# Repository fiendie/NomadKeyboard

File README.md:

# Nomad Keyboard

The Nomad is a 7×5 keys, column-staggered split keyboard based in part on the [Sofle Choc by Brian Low](https://github.com/brianlow/SofleKeyboard).
It uses low profile Kailh Choc v1 switches with hotswap sockets and features per-key RGB lighting via SK6812 Mini-E LEDs.
Compared to the Sofle Choc the nomad offers an additional thumb cluster key, an additional modifier key in the 5th row and a 7th inner column with 3 keys each.
An MX version is also available.

If you are a non-EU resident you can buy pre-made keyboards from [Lucky Boy Store](https://www.aliexpress.com/item/1005009922158971.html) on AliExpress.

## Table of Contents

- [Firmware](#firmware)
- [Bill of Materials](#bill-of-materials)
- [Default Layout](#default-layout)
- [Build Instructions](#build-instructions)
- [Images](#images)

## Firmware 

Nomad uses [QMK firmware](https://github.com/fiendie/qmk_firmware/tree/nomad)

Currently there is a default keymap for and a vial keymap to configure your keyboard in real time.

## Bill of Materials

| **Item**                                 | **Quantity** | **Notes**                                                                       |
|------------------------------------------|--------------|---------------------------------------------------------------------------------|
| **Nomad PCB**                            | 2            | Custom left and right halves.                                                   |
| **Kailh Choc v1 or MX switches**         | 68           | Choose based on version, the Choc version is only compatible with v1 switches!. |
| **Keycaps (MBK, ChocFox, or MX)**        | 68           | Must match switch type and profile preference.                                  |
| **SMD Diodes (1N4148, 0805 package)**    | 68           | One per switch; surface-mount only.                                             |
| **SK6812 Mini-E LEDs**                   | 68           | One per switch, make sure you get the Mini-E version specifically.              |
| **RP2040 Controller**                    | 2            | Tested with SplitKB Liatris and 42.Keebs Frood.                                 |
| **TRRS jacks**                           | 2            | For inter-half communication.                                                   |
| **TRRS cable**                           | 1            | Male-to-male, preferrably with 90 degree plugs                                  |
| **ALPS EC12 Low-Profile Rotary Encoder** | 2            | Optional rotary input.                                                          |
| **Tactile Reset Button**                 | 2            | Optional but useful.                                                            |
| **OLED Display (SSD1306 128x32)**        | 2 (optional) | Optional I2C displays.                                                          |
| **SMD Resistors (0805 package)**         | 4            | I2C pull-up resistors, ony needed for the displays                              |
| **Header Pins**                          | Varies       | For MCU, OLEDs.                                                                 |
| **3D-Printed Case**                      | 2 halves     | Top shell only; open-bottom design using included STL files.                    |
| **Acrylic Cover**                        | 2 halves     | Laser-cut cover layer using included DXF file.                                  |
| **M2 Standoffs (12 mm)**                 | 8            | For mounting cover to case.                                                     |
| **M2 Countersunk Screws (top)**          | 8            | For securing the acrylic cover to standoffs.                                    |
| **M2 Hex Screws (bottom of standoffs)**  | 8            | Attach standoffs from underneath the case edge.                                 |
| **Rubber feet**                          | 8+           | Optional, for grip and elevation.                                               |

## Default layout 

**Base Layer**
```
┌──────┬─────┬─────┬─────┬─────┬─────┬─────┐                ┌─────┬─────┬─────┬─────┬─────┬─────┬──────┐
│ Esc  │  1  │  2  │  3  │  4  │  5  │  <  │                │  >  │  6  │  7  │  8  │  9  │  0  │ Bksp │
├──────┼─────┼─────┼─────┼─────┼─────┼─────┤                ├─────┼─────┼─────┼─────┼─────┼─────┼──────┤
│ Tab  │  Q  │  W  │  E  │  R  │  T  │  {  │                │  }  │  Z  │  U  │  I  │  O  │  P  │  ?   │
├──────┼─────┼─────┼─────┼─────┼─────┼─────┤                ├─────┼─────┼─────┼─────┼─────┼─────┼──────┤
│  =   │  A  │  S  │  D  │  F  │  G  │  |  │                │  -  │  H  │  J  │  K  │  L  │  +  │  #   │
├──────┼─────┼─────┼─────┼─────┼─────┼─────┘                └─────┼─────┼─────┼─────┼─────┼─────┼──────┤
│ LSft │  Y  │  X  │  C  │  V  │  B  │                            │  N  │  M  │  ,  │  .  │  ↑  │ RSft │
├──────┼─────┼─────┼─────┼─────┼─────┼─────┬─────┐    ┌─────┬─────┼─────┼─────┼─────┼─────┼─────┼──────┤
│ Ctrl │ L3  │ L2  │ Opt │ GUI │     │ Spc │ Del │    │ L1  │ Rtn │     │ GUI │ Opt │  ←  │  ↓  │  →   │
└──────┴─────┴─────┴─────┴─────┘     └─────┴─────┘    └─────┴─────┘     └─────┴─────┴─────┴─────┴──────┘
```
**Symbol Layer**
```
┌──────┬─────┬─────┬─────┬─────┬─────┬─────┐                ┌─────┬─────┬─────┬─────┬─────┬─────┬──────┐
│      │     │     │     │     │     │  ^  │                │  °  │     │     │     │     │     │      │
├──────┼─────┼─────┼─────┼─────┼─────┼─────┤                ├─────┼─────┼─────┼─────┼─────┼─────┼──────┤
│      │  Q  │     │  €  │     │     │  [  │                │  ]  │     │  Ü  │     │  Ö  │     │      │
├──────┼─────┼─────┼─────┼─────┼─────┼─────┤                ├─────┼─────┼─────┼─────┼─────┼─────┼──────┤
│      │  Ä  │  ß  │     │     │     │  \  │                │  /  │  H  │     │     │  @  │     │      │
├──────┼─────┼─────┼─────┼─────┼─────┼─────┘                └─────┼─────┼─────┼─────┼─────┼─────┼──────┤
│      │     │     │     │     │     │                            │  ~  │     │     │     │     │      │
├──────┼─────┼─────┼─────┼─────┼─────┼─────┬─────┐    ┌─────┬─────┼─────┼─────┼─────┼─────┼─────┼──────┤
│      │     │     │     │     │     │     │     │    │     │     │     │     │     │     │     │      │
└──────┴─────┴─────┴─────┴─────┘     └─────┴─────┘    └─────┴─────┘     └─────┴─────┴─────┴─────┴──────┘
```
**FN/Media Layer**
```
┌──────┬─────┬─────┬─────┬─────┬─────┬─────┐                ┌─────┬─────┬─────┬─────┬─────┬─────┬──────┐
│      │ F1  │ F2  │ F3  │ F4  │ F5  │ F6  │                │ F7  │ F8  │ F9  │ F10 │ F11 │ F12 │      │
├──────┼─────┼─────┼─────┼─────┼─────┼─────┤                ├─────┼─────┼─────┼─────┼─────┼─────┼──────┤
│      │     │     │     │     │     │     │                │ B+  │     │     │     │     │     │      │
├──────┼─────┼─────┼─────┼─────┼─────┼─────┤                ├─────┼─────┼─────┼─────┼─────┼─────┼──────┤
│      │     │     │     │     │     │     │                │ B-  │     │     │     │     │     │      │
├──────┼─────┼─────┼─────┼─────┼─────┼─────┘                └─────┼─────┼─────┼─────┼─────┼─────┼──────┤
│      │     │     │     │     │     │                            │     │     │     │     │ PgU │ Ins  │
├──────┼─────┼─────┼─────┼─────┼─────┼─────┬─────┐    ┌─────┬─────┼─────┼─────┼─────┼─────┼─────┼──────┤
│      │     │     │     │ Rwd │     │ Pla │ Mut │    │ V-  │ V+  │     │ Fwd │     │ Hom │ PgD │ End  │
└──────┴─────┴─────┴─────┴─────┘     └─────┴─────┘    └─────┴─────┘     └─────┴─────┴─────┴─────┴──────┘
```
**RGB Settings Layer**
```
┌──────┬─────┬─────┬─────┬─────┬─────┬─────┐                ┌─────┬─────┬─────┬─────┬─────┬─────┬──────┐
│      │     │     │     │     │     │ Tgl │                │     │     │     │     │     │     │      │
├──────┼─────┼─────┼─────┼─────┼─────┼─────┤                ├─────┼─────┼─────┼─────┼─────┼─────┼──────┤
│      │     │     │     │     │     │ Md- │                │ Md+ │     │     │     │     │     │      │
├──────┼─────┼─────┼─────┼─────┼─────┼─────┤                ├─────┼─────┼─────┼─────┼─────┼─────┼──────┤
│      │     │     │     │     │     │ Sp- │                │ Sp+ │     │     │     │     │     │      │
├──────┼─────┼─────┼─────┼─────┼─────┼─────┘                └─────┼─────┼─────┼─────┼─────┼─────┼──────┤
│      │     │     │     │     │     │                            │     │     │     │     │     │      │
├──────┼─────┼─────┼─────┼─────┼─────┼─────┬─────┐    ┌─────┬─────┼─────┼─────┼─────┼─────┼─────┼──────┤
│      │     │     │     │ Va- │     │ H-  │ H+  │    │ S-  │ S+  │     │ Va+ │     │     │     │      │
└──────┴─────┴─────┴─────┴─────┘     └─────┴─────┘    └─────┴─────┘     └─────┴─────┴─────┴─────┴──────┘
```

## Build Instructions

Still a work in progress

## Images

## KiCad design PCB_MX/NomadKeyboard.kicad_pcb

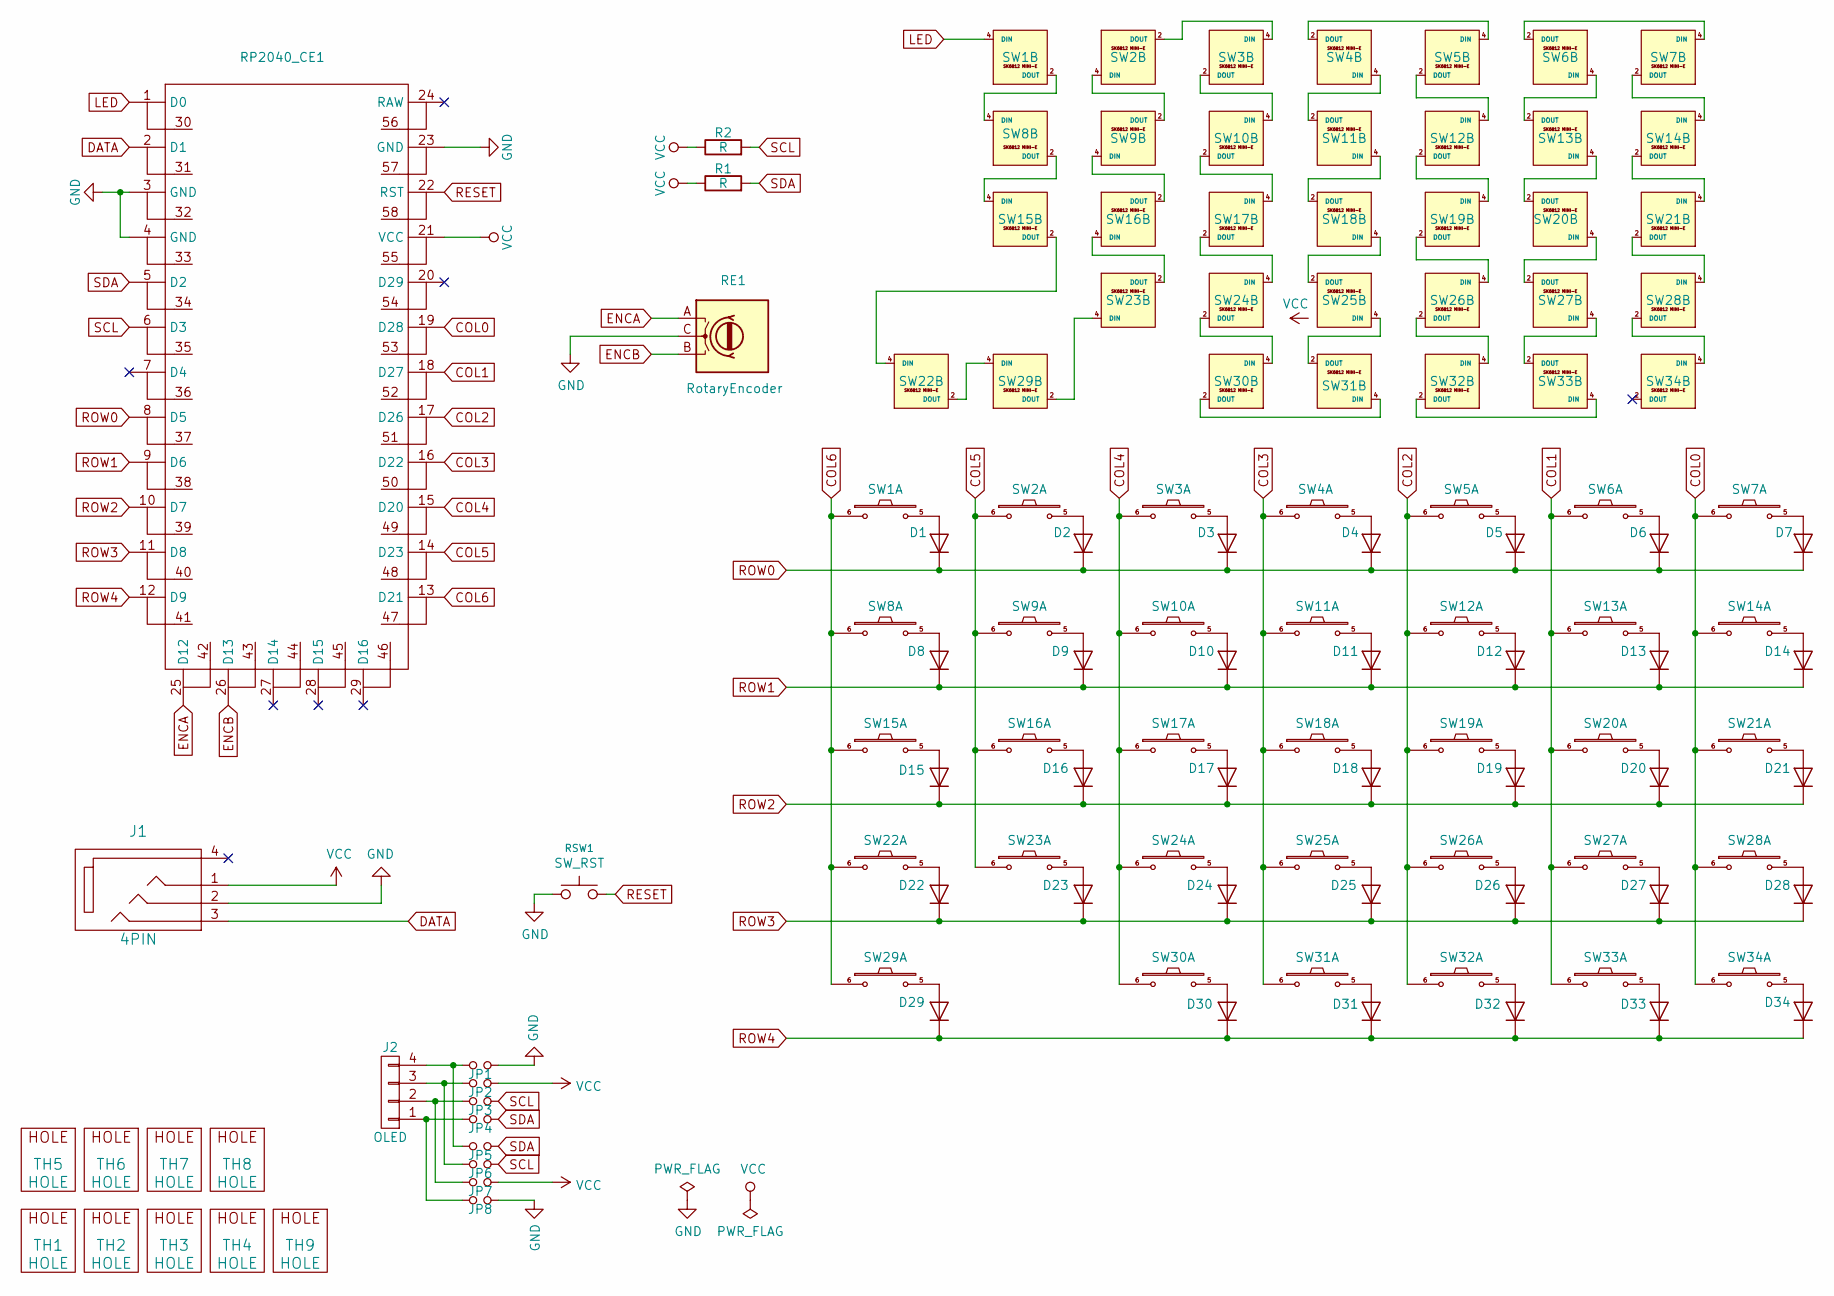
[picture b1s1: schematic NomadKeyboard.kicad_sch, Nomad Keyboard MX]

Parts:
D1, D2, D3, D4, D5, D6, D7, D8, D9, D10, D11, D12, D13, D14, D15, D16, D17, D18, D19, D20, D21, D22, D23, D24, D25, D26, D27, D28, D29, D30, D31, D32, D33, D34: D; crkbd-diode
J1: 4PIN; MJ-4PP-9
J2: OLED; OLED_4Pin
JP1, JP2, JP3, JP4, JP5, JP6, JP7, JP8: Jumper_NO_Small; Jumper
R1, R2: R; R_1206_3216Metric_Pad1.30x1.75mm_HandSolder
RE1: RotaryEncoder; RotaryEncoder_Alps_EC12E_Vertical_H20mm
RP2040_CE1: RP2040_CE
RSW1: SW_RST; TACT_SWITCH_TVBP06
SW1, SW2, SW3, SW4, SW5, SW6, SW7, SW8, SW9, SW10, SW11, SW12, SW13, SW14, SW15, SW16, SW17, SW18, SW19, SW20, SW21, SW22, SW23, SW24, SW25, SW26, SW27, SW28, SW29, SW30, SW31, SW32, SW33, SW34: SW_PUSH_LED; SK6812MINI-E_and_cherry
TH1, TH2, TH3, TH4, TH9: HOLE; HOLE_M2_TH
TH5, TH6, TH7, TH8: HOLE; M2_HOLE_PCB

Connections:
COL0: RP2040_CE1.19 (D28), SW7.6, SW14.6, SW21.6, SW28.6, SW34.6
COL1: RP2040_CE1.18 (D27), SW6.6, SW13.6, SW20.6, SW27.6, SW33.6
COL2: RP2040_CE1.17 (D26), SW5.6, SW12.6, SW19.6, SW26.6, SW32.6
COL3: RP2040_CE1.16 (D22), SW4.6, SW11.6, SW18.6, SW25.6, SW31.6
COL4: RP2040_CE1.15 (D20), SW3.6, SW10.6, SW17.6, SW24.6, SW30.6
COL5: RP2040_CE1.14 (D23), SW2.6, SW9.6, SW16.6, SW23.6
COL6: RP2040_CE1.13 (D21), SW1.6, SW8.6, SW15.6, SW22.6, SW29.6
DATA: J1.3, RP2040_CE1.2 (D1)
ENCA: RE1.A, RP2040_CE1.25 (D12)
ENCB: RE1.B, RP2040_CE1.26 (D13)
GND: J1.2, JP1.2, JP8.2, RE1.C, RP2040_CE1.3 (GND), RP2040_CE1.4 (GND), RP2040_CE1.23 (GND), RSW1.1, SW1.3 (GND), SW2.3 (GND), SW3.3 (GND), SW4.3 (GND), SW5.3 (GND), SW6.3 (GND), SW7.3 (GND), SW8.3 (GND), SW9.3 (GND), SW10.3 (GND), SW11.3 (GND), SW12.3 (GND), SW13.3 (GND), SW14.3 (GND), SW15.3 (GND), SW16.3 (GND), SW17.3 (GND), SW18.3 (GND), SW19.3 (GND), SW20.3 (GND), SW21.3 (GND), SW22.3 (GND), SW23.3 (GND), SW24.3 (GND), SW25.3 (GND), SW26.3 (GND), SW27.3 (GND), SW28.3 (GND), SW29.3 (GND), SW30.3 (GND), SW31.3 (GND), SW32.3 (GND), SW33.3 (GND), SW34.3 (GND)
LED: RP2040_CE1.1 (D0), SW1.4 (DIN)
unnamed: D1.2 (A), SW1.5
unnamed: D2.2 (A), SW2.5
unnamed: D3.2 (A), SW3.5
unnamed: D4.2 (A), SW4.5
unnamed: D5.2 (A), SW5.5
unnamed: D6.2 (A), SW6.5
unnamed: D7.2 (A), SW7.5
unnamed: D8.2 (A), SW8.5
unnamed: D9.2 (A), SW9.5
unnamed: D10.2 (A), SW10.5
unnamed: D11.2 (A), SW11.5
unnamed: D12.2 (A), SW12.5
unnamed: D13.2 (A), SW13.5
unnamed: D14.2 (A), SW14.5
unnamed: D15.2 (A), SW15.5
unnamed: D16.2 (A), SW16.5
unnamed: D17.2 (A), SW17.5
unnamed: D18.2 (A), SW18.5
unnamed: D19.2 (A), SW19.5
unnamed: D20.2 (A), SW20.5
unnamed: D21.2 (A), SW21.5
unnamed: D22.2 (A), SW22.5
unnamed: D23.2 (A), SW23.5
unnamed: D24.2 (A), SW24.5
unnamed: D25.2 (A), SW25.5
unnamed: D26.2 (A), SW26.5
unnamed: D27.2 (A), SW27.5
unnamed: D28.2 (A), SW28.5
unnamed: D29.2 (A), SW29.5
unnamed: D30.2 (A), SW30.5
unnamed: D31.2 (A), SW31.5
unnamed: D32.2 (A), SW32.5
unnamed: D33.2 (A), SW33.5
unnamed: D34.2 (A), SW34.5
unnamed: J2.1, JP4.1, JP8.1
unnamed: J2.2, JP3.1, JP7.1
unnamed: J2.3, JP2.1, JP6.1
unnamed: J2.4, JP1.1, JP5.1
unnamed: SW1.2 (DOUT), SW8.4 (DIN)
unnamed: SW2.4 (DIN), SW9.2 (DOUT)
unnamed: SW2.2 (DOUT), SW3.4 (DIN)
unnamed: SW4.2 (DOUT), SW5.4 (DIN)
unnamed: SW6.2 (DOUT), SW7.4 (DIN)
unnamed: SW3.2 (DOUT), SW10.4 (DIN)
unnamed: SW10.2 (DOUT), SW17.4 (DIN)
unnamed: SW11.4 (DIN), SW18.2 (DOUT)
unnamed: SW4.4 (DIN), SW11.2 (DOUT)
unnamed: SW5.2 (DOUT), SW12.4 (DIN)
unnamed: SW12.2 (DOUT), SW19.4 (DIN)
unnamed: SW13.4 (DIN), SW20.2 (DOUT)
unnamed: SW6.4 (DIN), SW13.2 (DOUT)
unnamed: SW7.2 (DOUT), SW14.4 (DIN)
unnamed: SW14.2 (DOUT), SW21.4 (DIN)
unnamed: SW8.2 (DOUT), SW15.4 (DIN)
unnamed: SW15.2 (DOUT), SW22.4 (DIN)
unnamed: SW16.4 (DIN), SW23.2 (DOUT)
unnamed: SW9.4 (DIN), SW16.2 (DOUT)
unnamed: SW17.2 (DOUT), SW24.4 (DIN)
unnamed: SW18.4 (DIN), SW25.2 (DOUT)
unnamed: SW19.2 (DOUT), SW26.4 (DIN)
unnamed: SW20.4 (DIN), SW27.2 (DOUT)
unnamed: SW21.2 (DOUT), SW28.4 (DIN)
unnamed: SW22.2 (DOUT), SW29.4 (DIN)
unnamed: SW23.4 (DIN), SW29.2 (DOUT)
unnamed: SW24.2 (DOUT), SW30.4 (DIN)
unnamed: SW25.4 (DIN), SW31.2 (DOUT)
unnamed: SW26.2 (DOUT), SW32.4 (DIN)
unnamed: SW27.4 (DIN), SW33.2 (DOUT)
unnamed: SW28.2 (DOUT), SW34.4 (DIN)
unnamed: SW30.2 (DOUT), SW31.4 (DIN)
unnamed: SW32.2 (DOUT), SW33.4 (DIN)
RESET: RP2040_CE1.22 (RST), RSW1.2
ROW0: D1.1 (K), D2.1 (K), D3.1 (K), D4.1 (K), D5.1 (K), D6.1 (K), D7.1 (K), RP2040_CE1.8 (D5)
ROW1: D8.1 (K), D9.1 (K), D10.1 (K), D11.1 (K), D12.1 (K), D13.1 (K), D14.1 (K), RP2040_CE1.9 (D6)
ROW2: D15.1 (K), D16.1 (K), D17.1 (K), D18.1 (K), D19.1 (K), D20.1 (K), D21.1 (K), RP2040_CE1.10 (D7)
ROW3: D22.1 (K), D23.1 (K), D24.1 (K), D25.1 (K), D26.1 (K), D27.1 (K), D28.1 (K), RP2040_CE1.11 (D8)
ROW4: D29.1 (K), D30.1 (K), D31.1 (K), D32.1 (K), D33.1 (K), D34.1 (K), RP2040_CE1.12 (D9)
SCL: JP3.2, JP6.2, R2.2, RP2040_CE1.6 (D3)
SDA: JP4.2, JP5.2, R1.2, RP2040_CE1.5 (D2)
VCC: J1.1, JP2.2, JP7.2, R1.1, R2.1, RP2040_CE1.21 (VCC), SW1.1 (VDD), SW2.1 (VDD), SW3.1 (VDD), SW4.1 (VDD), SW5.1 (VDD), SW6.1 (VDD), SW7.1 (VDD), SW8.1 (VDD), SW9.1 (VDD), SW10.1 (VDD), SW11.1 (VDD), SW12.1 (VDD), SW13.1 (VDD), SW14.1 (VDD), SW15.1 (VDD), SW16.1 (VDD), SW17.1 (VDD), SW18.1 (VDD), SW19.1 (VDD), SW20.1 (VDD), SW21.1 (VDD), SW22.1 (VDD), SW23.1 (VDD), SW24.1 (VDD), SW25.1 (VDD), SW26.1 (VDD), SW27.1 (VDD), SW28.1 (VDD), SW29.1 (VDD), SW30.1 (VDD), SW31.1 (VDD), SW32.1 (VDD), SW33.1 (VDD), SW34.1 (VDD)

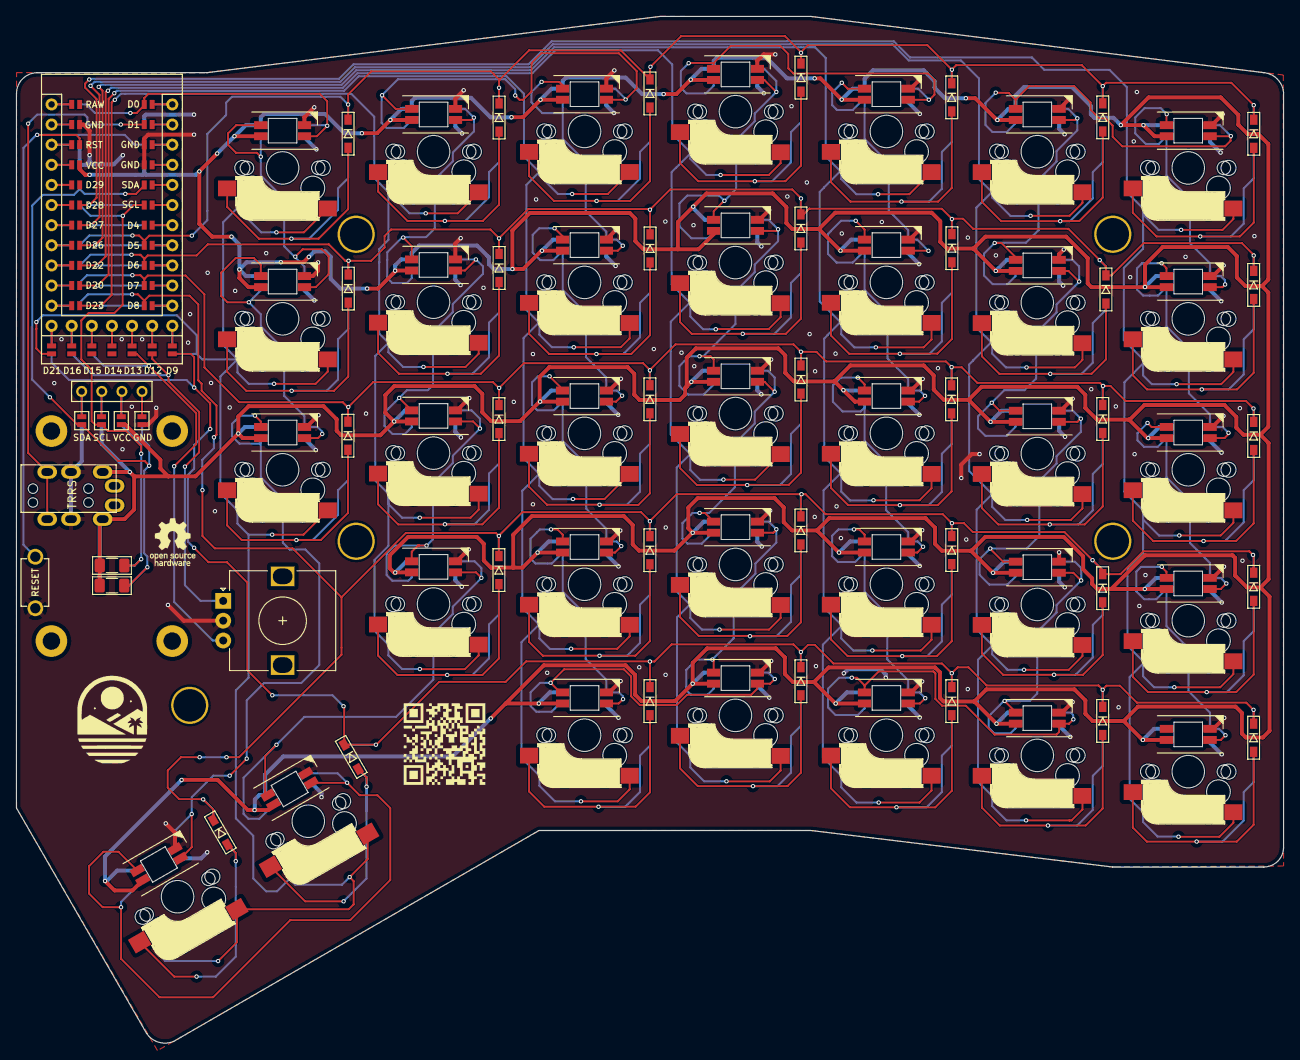
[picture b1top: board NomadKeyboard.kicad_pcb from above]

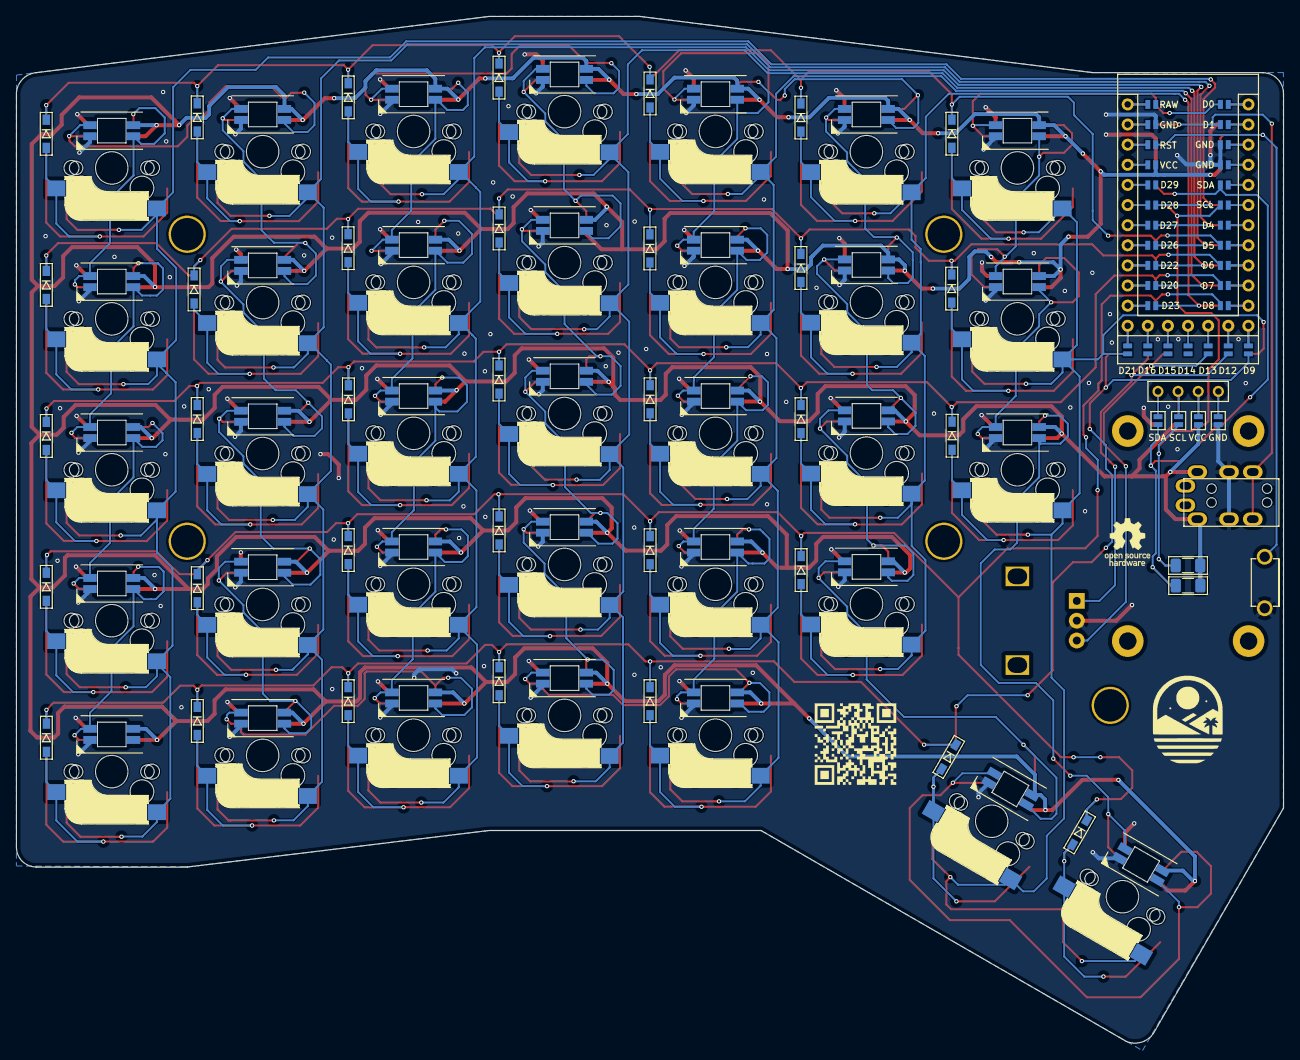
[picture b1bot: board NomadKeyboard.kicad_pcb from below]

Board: 2 copper layers, 159.9 x 129.6 mm, 98 parts (7 on the bottom side), 92 nets.

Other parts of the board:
L1, L2: LOGO; Nomad_Logo_20
OH1, OH2: OSHW-Logo_5.7x6mm_SilkScreen
QR1, QR2: QRCODE; Nomad_QR_Code

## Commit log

2024-08-16 First revision of the Nomad keyboard PCB
2024-08-18 Additional mounting hole, Logo and QR Code on Silkscreen
2024-08-22 Added Images of the finished keyboard
2024-09-16 Plated Mounting holes, STL File for top case, new Photos
2024-10-26 added new buttons
2024-10-27 added new buttons wip
2024-10-27 Finished, updated gerber files
2024-10-28 added footprint for rp2040
2024-11-09 Added a new MX variant of the PCB, moved mounting holes for the display cover so the spacers don't interfere with the display
2024-11-13 Rotated thumb cluster keys on the MX version for 1.5U shine-through blank key caps
2024-11-13 Add tenting case for MX Version
2024-11-13 Update Gerber files for MX version
2024-11-27 Updated tenting case for MX version, added variant without tenting
2025-01-12 Nomad Rev 2
    * Exclusively supports RP2040 CE microcontrollers
    * Only one set of headers for hte RP2040 with solder jumpers to select
    the half
    * EC12 low-profile rotary encoder support
2025-01-14 Tweaked position of rotary encoder, updated Gerber files
2025-04-20 Updated page settings
2025-04-20 Addec BoM, updated photos
2025-04-20 Added base layer of default keymap to README
2025-04-20 Added other layers of the default layout to the README, updated intro text
2025-04-20 Fixed wrong symbols in README
2025-11-24 Updated README to incorporate store link, mention vial keymap and add LEDs to BOM
